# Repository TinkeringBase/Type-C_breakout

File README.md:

[한국어](https://github.com/TinkeringBase/Type-C_breakout/blob/kicad/readme-ko.md)
# TinkeringBase Type C breakout
\
ESD-Safe USB Type C power breakout that act as upstream-facing port, UFP, aka "peripheral device" and draws 5V from host device. It can draw current up to 3A. It can be held in place with two M2 bolts. It can transfer USB 2.0 data. It has 3-channel TVS so it is safe from ESD.
## pinout
VB - VBUS\
DP - Data Positive\
DN - Data Negative\
G - Ground

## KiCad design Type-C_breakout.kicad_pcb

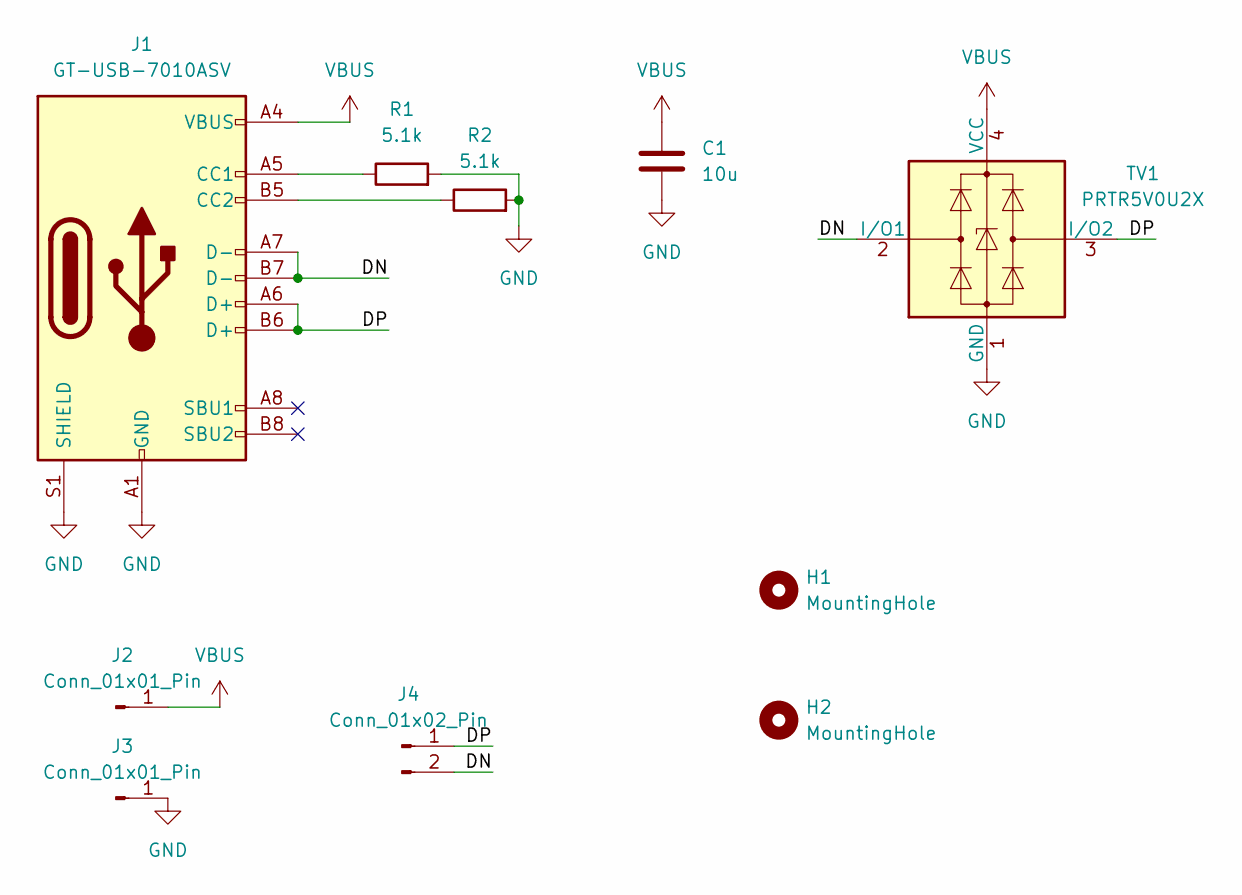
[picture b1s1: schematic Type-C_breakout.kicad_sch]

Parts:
C1: 10u; C_0603_1608Metric
H1, H2: MountingHole; MountingHole_2.2mm_M2
J1: GT-USB-7010ASV; USB_C_Receptacle_G-Switch_GT-USB-7010ASV
J2, J3: Conn_01x01_Pin; PinHeader_1x01_P2.54mm_Vertical
J4: Conn_01x02_Pin; PinHeader_1x02_P2.54mm_Vertical
R1, R2: 5.1k; R_0402_1005Metric
TV1: PRTR5V0U2X; SOT-143

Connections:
/DN: J1.A7 (D-), J1.B7 (D-), J4.2, TV1.2 (I/O1)
/DP: J1.A6 (D+), J1.B6 (D+), J4.1, TV1.3 (I/O2)
GND: C1.2, J1.A1 (GND), J1.A12 (GND), J1.B1 (GND), J1.B12 (GND), J1.S1 (SHIELD), J3.1, R1.2, R2.2, TV1.1 (GND)
unnamed: J1.A5 (CC1), R1.1
unnamed: J1.B5 (CC2), R2.1
VBUS: C1.1, J1.A4 (VBUS), J1.A9 (VBUS), J1.B4 (VBUS), J1.B9 (VBUS), J2.1, TV1.4 (VCC)

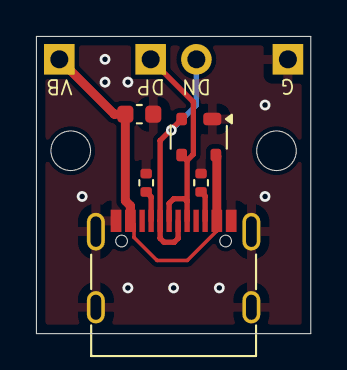
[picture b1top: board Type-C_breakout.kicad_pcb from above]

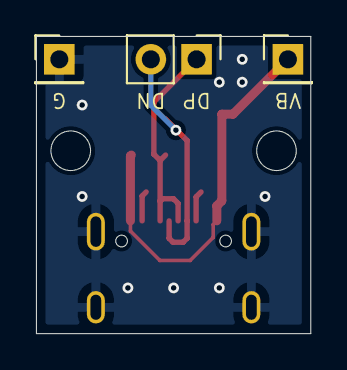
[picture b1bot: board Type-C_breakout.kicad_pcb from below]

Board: 2 copper layers, 15.2 x 16.5 mm, 10 parts (3 on the bottom side), 6 nets.

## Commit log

2024-04-17 rework to kicad
2024-04-17 fix readme preview image
2024-05-10 gitignore
